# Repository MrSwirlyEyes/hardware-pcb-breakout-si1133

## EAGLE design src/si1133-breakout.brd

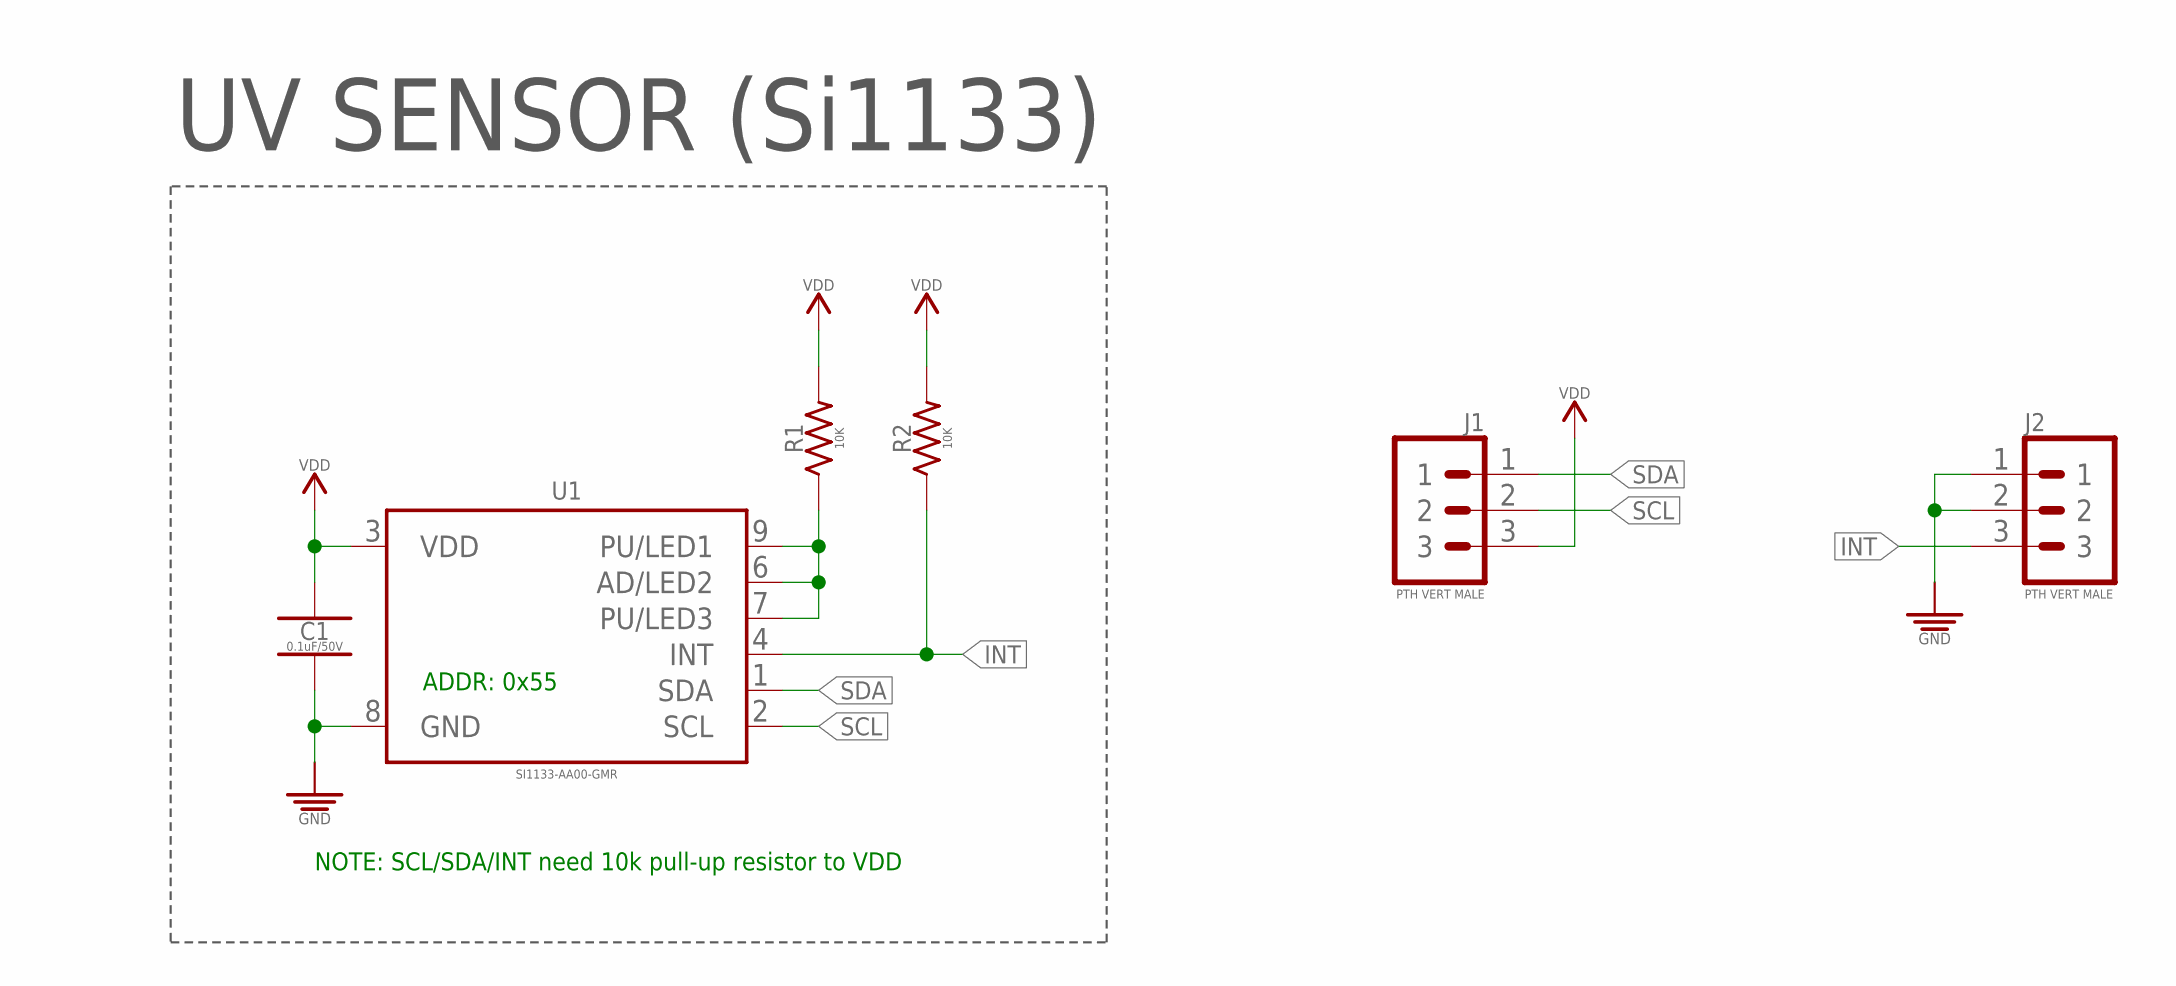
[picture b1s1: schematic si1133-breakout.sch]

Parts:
C1: 0.1uF/50V; CAPC1005X55_SMD-0402
J1, J2: PTH VERT MALE; HDRV3W64P254_1X3_762X254X838B
R1, R2: 10K; RESC1005X35_SMD-0402
U1: SI1133-AA00-GMR; QFN50P200X200X75-10N

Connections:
GND: C1.2, J2.1, J2.2, U1.8 (GND)
INT: J2.3, R2.1, U1.4 (INT)
unnamed: R1.1, U1.6 (AD/LED2), U1.7 (PU/LED3), U1.9 (PU/LED1)
SCL: J1.2, U1.2 (SCL)
SDA: J1.1, U1.1 (SDA)
VDD: C1.1, J1.3, R1.2, R2.2, U1.3 (VDD)

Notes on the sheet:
UV SENSOR (Si1133)
ADDR: 0x55
NOTE: SCL/SDA/INT need 10k pull-up resistor to VDD

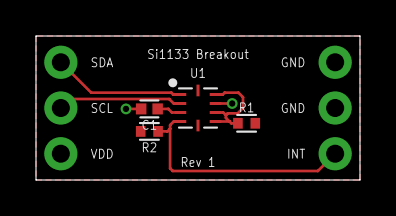
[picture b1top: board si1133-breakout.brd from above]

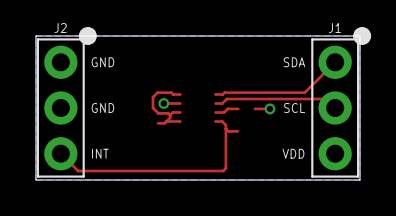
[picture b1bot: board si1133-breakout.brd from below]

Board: 2 copper layers, 18.0 x 8.0 mm, 6 parts (2 on the bottom side), 6 nets.

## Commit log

2021-01-12 [Rev 1] - Initialize repo.
2021-02-06 Update to fit OSH Park 2-layer DRU.
2021-08-11 Update CAM files.
